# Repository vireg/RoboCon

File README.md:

RoboCon-2014
============

The following libraries are currently in use:

Library for the digital IMU MPU-6050 from InvenSense (including Kalman filter) by Kristian Lauszus

PlayStation 2 Controller Arduino Library by Bill Porter

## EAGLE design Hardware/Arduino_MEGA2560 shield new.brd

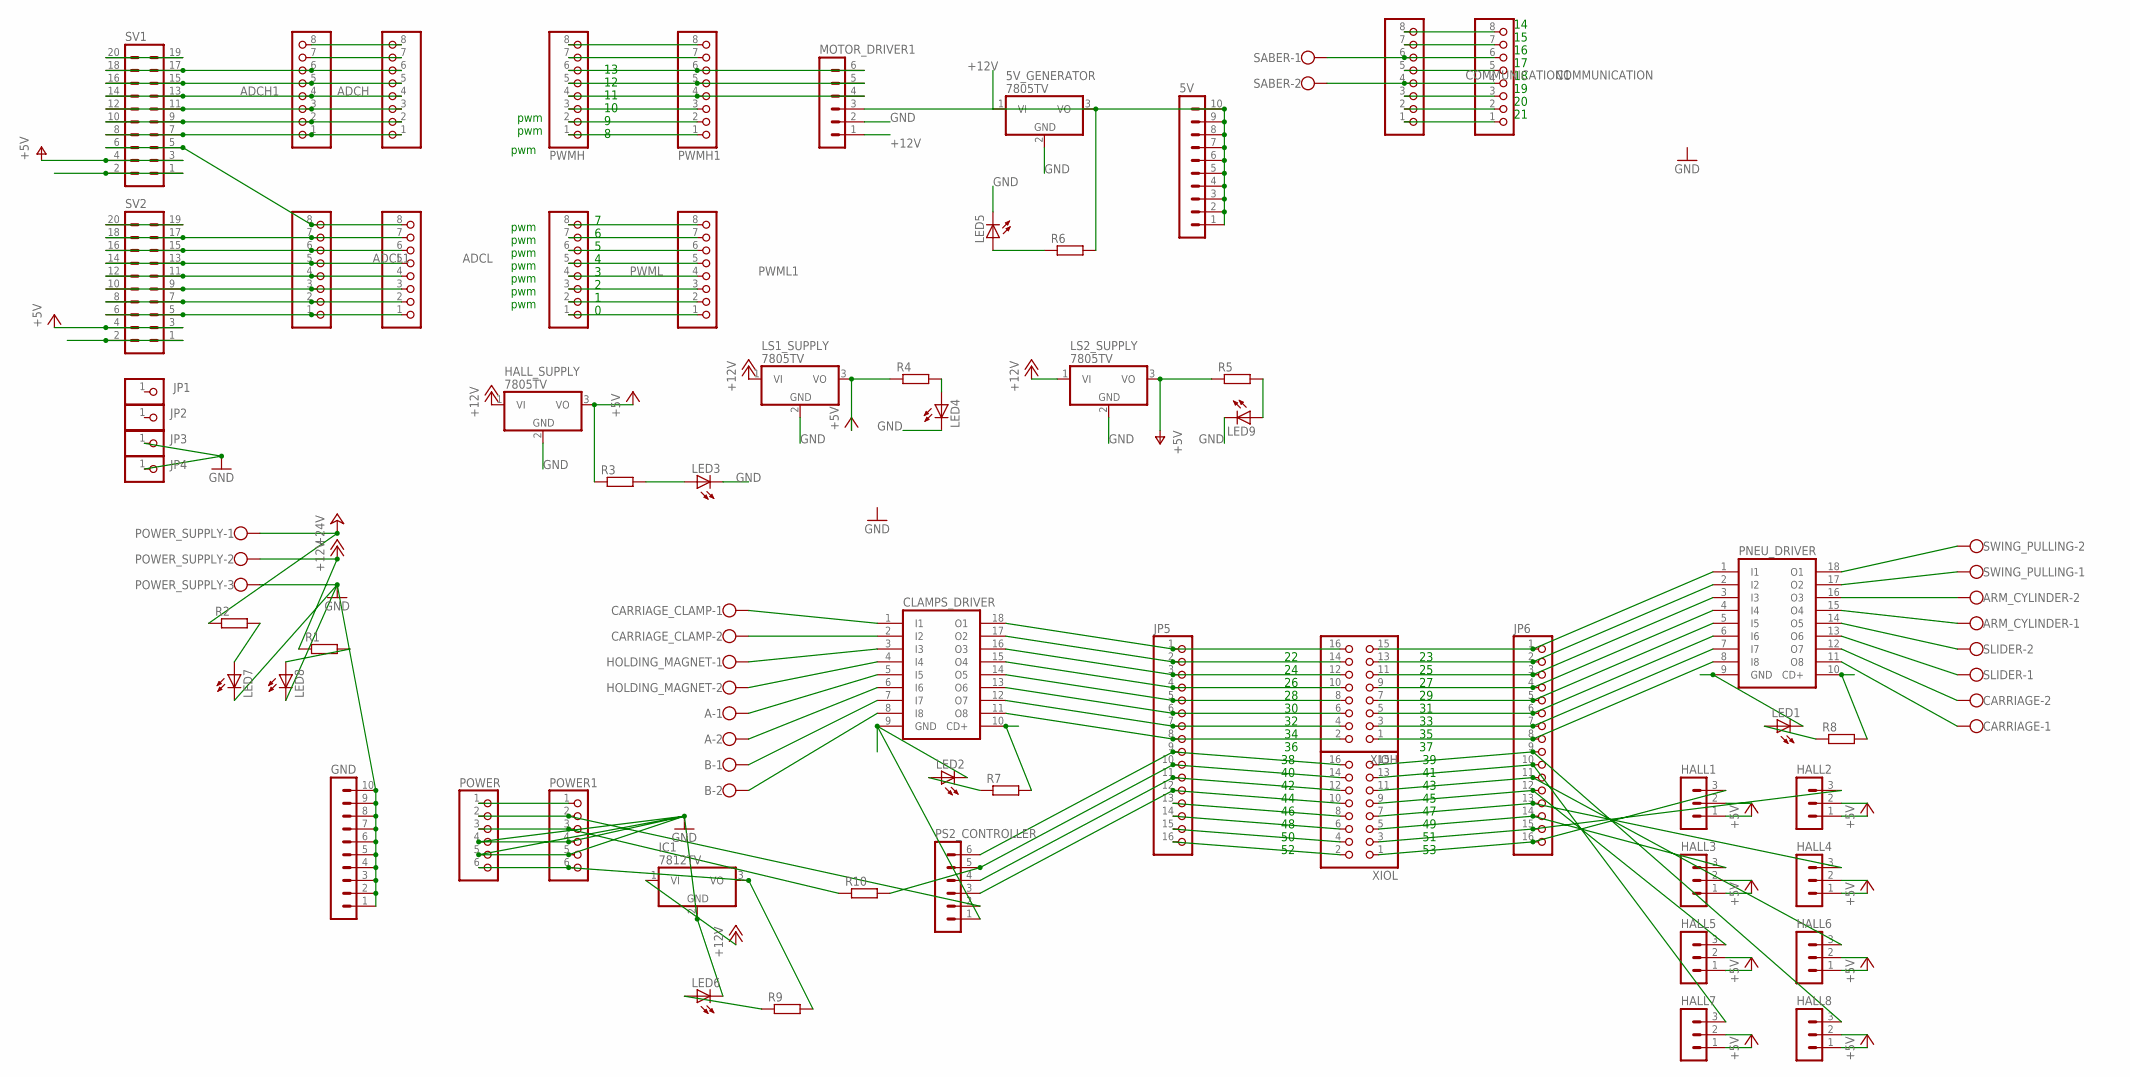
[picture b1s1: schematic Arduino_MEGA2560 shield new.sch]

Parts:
5V: MA10-1
5V_GENERATOR: 7805TV; TO220V
A: W237-102
ADCH, ADCH1: PINHD-1X8; 1X08
ADCL, ADCL1: PINHD-1X8; 1X08
ARM_CYLINDER: W237-102
B: W237-102
CARRIAGE: W237-102
CARRIAGE_CLAMP: W237-102
CLAMPS_DRIVER: ULN2803A; DIL18
COMMUNICATION, COMMUNICATION1: PINHD-1X8; 1X08
GND: MA10-1
HALL1, HALL2, HALL3, HALL4, HALL5, HALL6, HALL7, HALL8: MA03-1
HALL_SUPPLY: 7805TV; TO220V
HOLDING_MAGNET: W237-102
IC1: 7812TV; TO220V
JP1, JP2, JP3, JP4: PINHD-1X1; 1X01
JP5, JP6: PINHD-1X16; 1X16
LED1, LED2, LED3, LED4, LED5, LED6, LED7, LED8, LED9: LEDSML1206; SML1206
LS1_SUPPLY, LS2_SUPPLY: 7805TV; TO220V
MOTOR_DRIVER1: MA06-1
PNEU_DRIVER: ULN2803A; DIL18
POWER, POWER1: PINHD-1X6; 1X06
POWER_SUPPLY: W237-103
PS2_CONTROLLER: MA06-1
PWMH, PWMH1: PINHD-1X8; 1X08
PWML, PWML1: PINHD-1X8; 1X08
R1, R2, R3, R4, R5, R6, R7, R8, R9: R-EU_R0805; R0805
R10: R0204/7; 0204/7
SABER: W237-102
SLIDER: W237-102
SV1, SV2: MA10-2
SWING_PULLING: W237-102
XIOH: PINHD-2X8; 2X08
XIOL: PINHD-2X8; 2X08

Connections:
+5V: HALL1.1, HALL2.1, HALL3.1, HALL4.1, HALL5.1, HALL6.1, HALL7.1, HALL8.1, HALL_SUPPLY.3 (VO), R3.1
+12V: 5V_GENERATOR.1 (VI), HALL_SUPPLY.1 (VI), IC1.1 (VI), LS1_SUPPLY.1 (VI), LS2_SUPPLY.1 (VI), MOTOR_DRIVER1.1, POWER_SUPPLY.2, R1.1
+24V: CLAMPS_DRIVER.10 (CD+), PNEU_DRIVER.10 (CD+), POWER_SUPPLY.1, R2.1, R7.2, R8.2
GND: 5V_GENERATOR.2 (GND), CLAMPS_DRIVER.9 (GND), GND.1, GND.2, GND.3, GND.4, GND.5, GND.6, GND.7, GND.8, GND.9, GND.10, HALL1.2, HALL2.2, HALL3.2, HALL4.2, HALL5.2, HALL6.2, HALL7.2, HALL8.2, HALL_SUPPLY.2 (GND), IC1.2 (GND), JP3.1, JP4.1, LED1.C, LED2.C, LED3.C, LED4.C, LED5.C, LED6.C, LED7.C, LED8.C, LED9.C, LS1_SUPPLY.2 (GND), LS2_SUPPLY.2 (GND), MOTOR_DRIVER1.2, PNEU_DRIVER.9 (GND), POWER.4, POWER.5, POWER1.4, POWER1.5, POWER_SUPPLY.3, PS2_CONTROLLER.1, SV1.1, SV1.2, SV2.1, SV2.2
unnamed: PWMH.1, PWMH1.1
unnamed: PWMH.2, PWMH1.2
unnamed: PWMH.3, PWMH1.3
unnamed: MOTOR_DRIVER1.4, PWMH.4, PWMH1.4
unnamed: MOTOR_DRIVER1.5, PWMH.5, PWMH1.5
unnamed: MOTOR_DRIVER1.6, PWMH.6, PWMH1.6
unnamed: PWMH.7, PWMH1.7
unnamed: PWMH.8, PWMH1.8
unnamed: ADCH.8, ADCH1.8
unnamed: ADCH.6, ADCH1.6, SV1.17, SV1.18
unnamed: ADCH.5, ADCH1.5, SV1.15, SV1.16
unnamed: ADCH.4, ADCH1.4, SV1.13, SV1.14
unnamed: ADCH.3, ADCH1.3, SV1.11, SV1.12
unnamed: ADCH.2, ADCH1.2, SV1.9, SV1.10
unnamed: ADCH.1, ADCH1.1, SV1.7, SV1.8
unnamed: POWER.1, POWER1.1
unnamed: POWER.2, POWER1.2, PS2_CONTROLLER.2
unnamed: POWER.3, POWER1.3, R10.1
unnamed: IC1.3 (VO), POWER.6, POWER1.6, R9.2
unnamed: LED7.A, R2.2
unnamed: PNEU_DRIVER.18 (O1), SWING_PULLING.2
unnamed: COMMUNICATION.8, COMMUNICATION1.8
unnamed: COMMUNICATION.7, COMMUNICATION1.7
unnamed: COMMUNICATION.6, COMMUNICATION1.6, SABER.1
unnamed: COMMUNICATION.5, COMMUNICATION1.5
unnamed: COMMUNICATION.4, COMMUNICATION1.4, SABER.2
unnamed: COMMUNICATION.3, COMMUNICATION1.3
unnamed: COMMUNICATION.2, COMMUNICATION1.2
unnamed: COMMUNICATION.1, COMMUNICATION1.1
unnamed: PWML.8, PWML1.8
unnamed: PWML.7, PWML1.7
unnamed: PWML.6, PWML1.6
unnamed: PWML.5, PWML1.5
unnamed: PWML.4, PWML1.4
unnamed: PWML.3, PWML1.3
unnamed: PWML.2, PWML1.2
unnamed: PWML.1, PWML1.1
unnamed: ADCL.8, ADCL1.8, SV1.5, SV1.6
unnamed: ADCL.7, ADCL1.7, SV2.17, SV2.18
unnamed: ADCL.5, ADCL1.5, SV2.13, SV2.14
unnamed: ADCL.3, ADCL1.3, SV2.9, SV2.10
unnamed: ADCL.2, ADCL1.2, SV2.7, SV2.8
unnamed: ADCL.1, ADCL1.1, SV2.5, SV2.6
unnamed: CLAMPS_DRIVER.18 (O1), JP5.1, XIOH.16
unnamed: CLAMPS_DRIVER.17 (O2), JP5.2, XIOH.14
unnamed: CLAMPS_DRIVER.16 (O3), JP5.3, XIOH.12
unnamed: CLAMPS_DRIVER.15 (O4), JP5.4, XIOH.10
unnamed: CLAMPS_DRIVER.14 (O5), JP5.5, XIOH.8
unnamed: CLAMPS_DRIVER.13 (O6), JP5.6, XIOH.6
unnamed: CLAMPS_DRIVER.12 (O7), JP5.7, XIOH.4
unnamed: JP5.12, PS2_CONTROLLER.3, XIOL.10
unnamed: JP5.9, PS2_CONTROLLER.6, XIOL.16
unnamed: JP5.10, PS2_CONTROLLER.5, R10.2, XIOL.14
unnamed: JP5.11, PS2_CONTROLLER.4, XIOL.12
unnamed: JP5.13, XIOL.8
unnamed: JP5.14, XIOL.6
unnamed: JP5.15, XIOL.4
unnamed: JP6.1, PNEU_DRIVER.1 (I1), XIOH.15
unnamed: JP6.2, PNEU_DRIVER.2 (I2), XIOH.13
unnamed: JP6.3, PNEU_DRIVER.3 (I3), XIOH.11
unnamed: JP6.4, PNEU_DRIVER.4 (I4), XIOH.9
unnamed: JP6.5, PNEU_DRIVER.5 (I5), XIOH.7
unnamed: JP6.6, PNEU_DRIVER.6 (I6), XIOH.5
unnamed: JP6.7, PNEU_DRIVER.7 (I7), XIOH.3
unnamed: JP6.8, PNEU_DRIVER.8 (I8), XIOH.1
unnamed: HALL8.3, JP6.9, XIOL.15
unnamed: HALL7.3, JP6.10, XIOL.13
unnamed: HALL6.3, JP6.11, XIOL.11
unnamed: HALL5.3, JP6.12, XIOL.9
unnamed: HALL4.3, JP6.13, XIOL.7
unnamed: HALL3.3, JP6.14, XIOL.5
unnamed: JP5.16, XIOL.2
unnamed: HALL1.3, JP6.16, XIOL.1
unnamed: HALL2.3, JP6.15, XIOL.3
unnamed: CLAMPS_DRIVER.11 (O8), JP5.8, XIOH.2
unnamed: CARRIAGE_CLAMP.1, CLAMPS_DRIVER.1 (I1)
unnamed: PNEU_DRIVER.17 (O2), SWING_PULLING.1
unnamed: ARM_CYLINDER.2, PNEU_DRIVER.16 (O3)
unnamed: ARM_CYLINDER.1, PNEU_DRIVER.15 (O4)
unnamed: PNEU_DRIVER.14 (O5), SLIDER.2
unnamed: PNEU_DRIVER.13 (O6), SLIDER.1
unnamed: CARRIAGE.2, PNEU_DRIVER.12 (O7)
unnamed: CARRIAGE.1, PNEU_DRIVER.11 (O8)
unnamed: CARRIAGE_CLAMP.2, CLAMPS_DRIVER.2 (I2)
unnamed: CLAMPS_DRIVER.3 (I3), HOLDING_MAGNET.1
unnamed: CLAMPS_DRIVER.4 (I4), HOLDING_MAGNET.2
unnamed: A.1, CLAMPS_DRIVER.5 (I5)
unnamed: A.2, CLAMPS_DRIVER.6 (I6)
unnamed: B.1, CLAMPS_DRIVER.7 (I7)
unnamed: B.2, CLAMPS_DRIVER.8 (I8)
unnamed: LED8.A, R1.2
unnamed: LED3.A, R3.2
unnamed: LED4.A, R4.2
unnamed: LED9.A, R5.2
unnamed: 5V.1, 5V.2, 5V.3, 5V.4, 5V.5, 5V.6, 5V.7, 5V.8, 5V.9, 5V.10, 5V_GENERATOR.3 (VO), MOTOR_DRIVER1.3, R6.2
unnamed: LED5.A, R6.1
unnamed: LED6.A, R9.1
unnamed: LED1.A, R8.1
unnamed: LED2.A, R7.1
unnamed: ADCH.7, ADCH1.7
unnamed: SV2.19, SV2.20
unnamed: SV1.19, SV1.20
unnamed: ADCL.6, ADCL1.6, SV2.15, SV2.16
unnamed: ADCL.4, ADCL1.4, SV2.11, SV2.12
V+: LS2_SUPPLY.3 (VO), R5.1, SV1.3, SV1.4
VCC: LS1_SUPPLY.3 (VO), R4.1, SV2.3, SV2.4

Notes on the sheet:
pwm

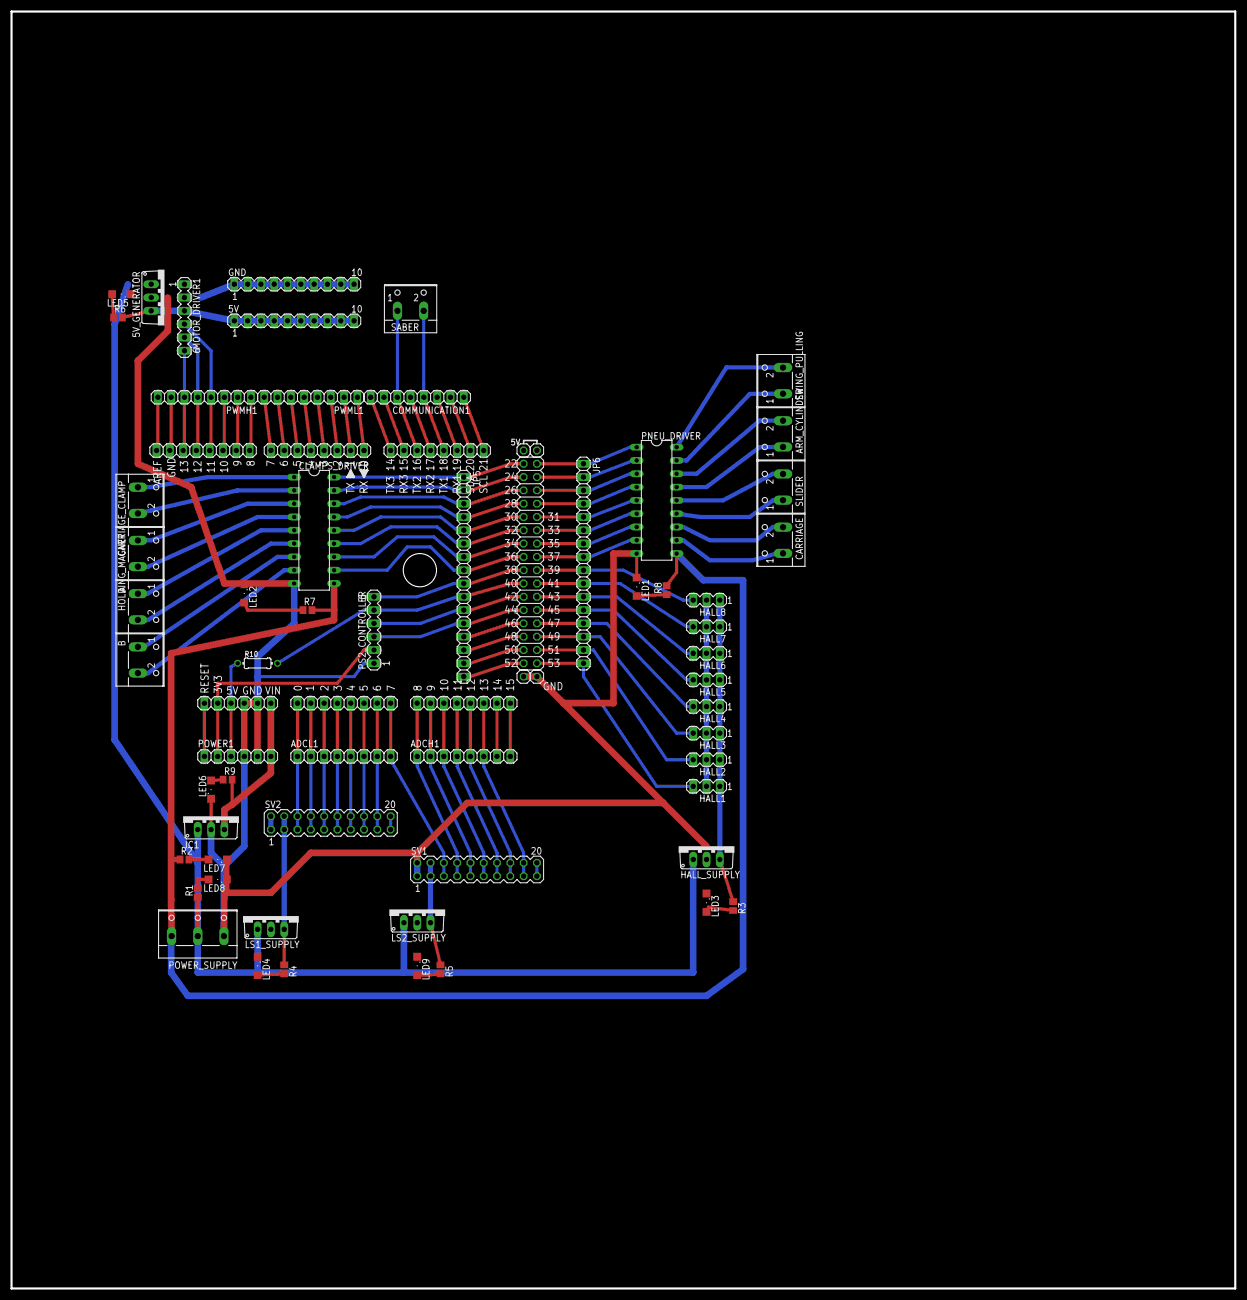
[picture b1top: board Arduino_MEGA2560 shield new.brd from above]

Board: 2 copper layers, 233.7 x 243.8 mm, 70 parts (0 on the bottom side), 110 nets.

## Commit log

2014-01-11 PS2 code for controlling motors...
2014-01-11 Renamed PS2X arduino file
2014-01-11 MPU6050 libary for arduino by Jeff Rowberg.
2014-01-11 removed MPU6050 files.
2014-01-11 Removed PS2 library.
2014-01-11 Code for PS2 controller using library created by Bill Porter.
2014-01-11 MPU6050 code for arduino by Jeff Rowberg.
2014-01-11 Renamed Folder.
2014-02-05 Updated with code for Sabertooth motor drivers.
2014-02-06 Added interface for hall sensors to control pneumatics.
2014-02-13 Sketch for IMU MPU6050(including Kalman filter) by Kristian Lauszus
2014-02-13 Modified code to calculate yaw values.
2014-02-13 Edited README.
2014-02-23 Final integration
2014-02-25 added pneumatics drivers.
2014-02-25 Modified modes methods.
2014-02-27 code for the autonomous robot.
2014-03-12 Cleanup.
2014-03-12 Added Line Following & PID
2014-03-12 Final code used at Robocon India - 2014
2015-02-06 Adding board files
